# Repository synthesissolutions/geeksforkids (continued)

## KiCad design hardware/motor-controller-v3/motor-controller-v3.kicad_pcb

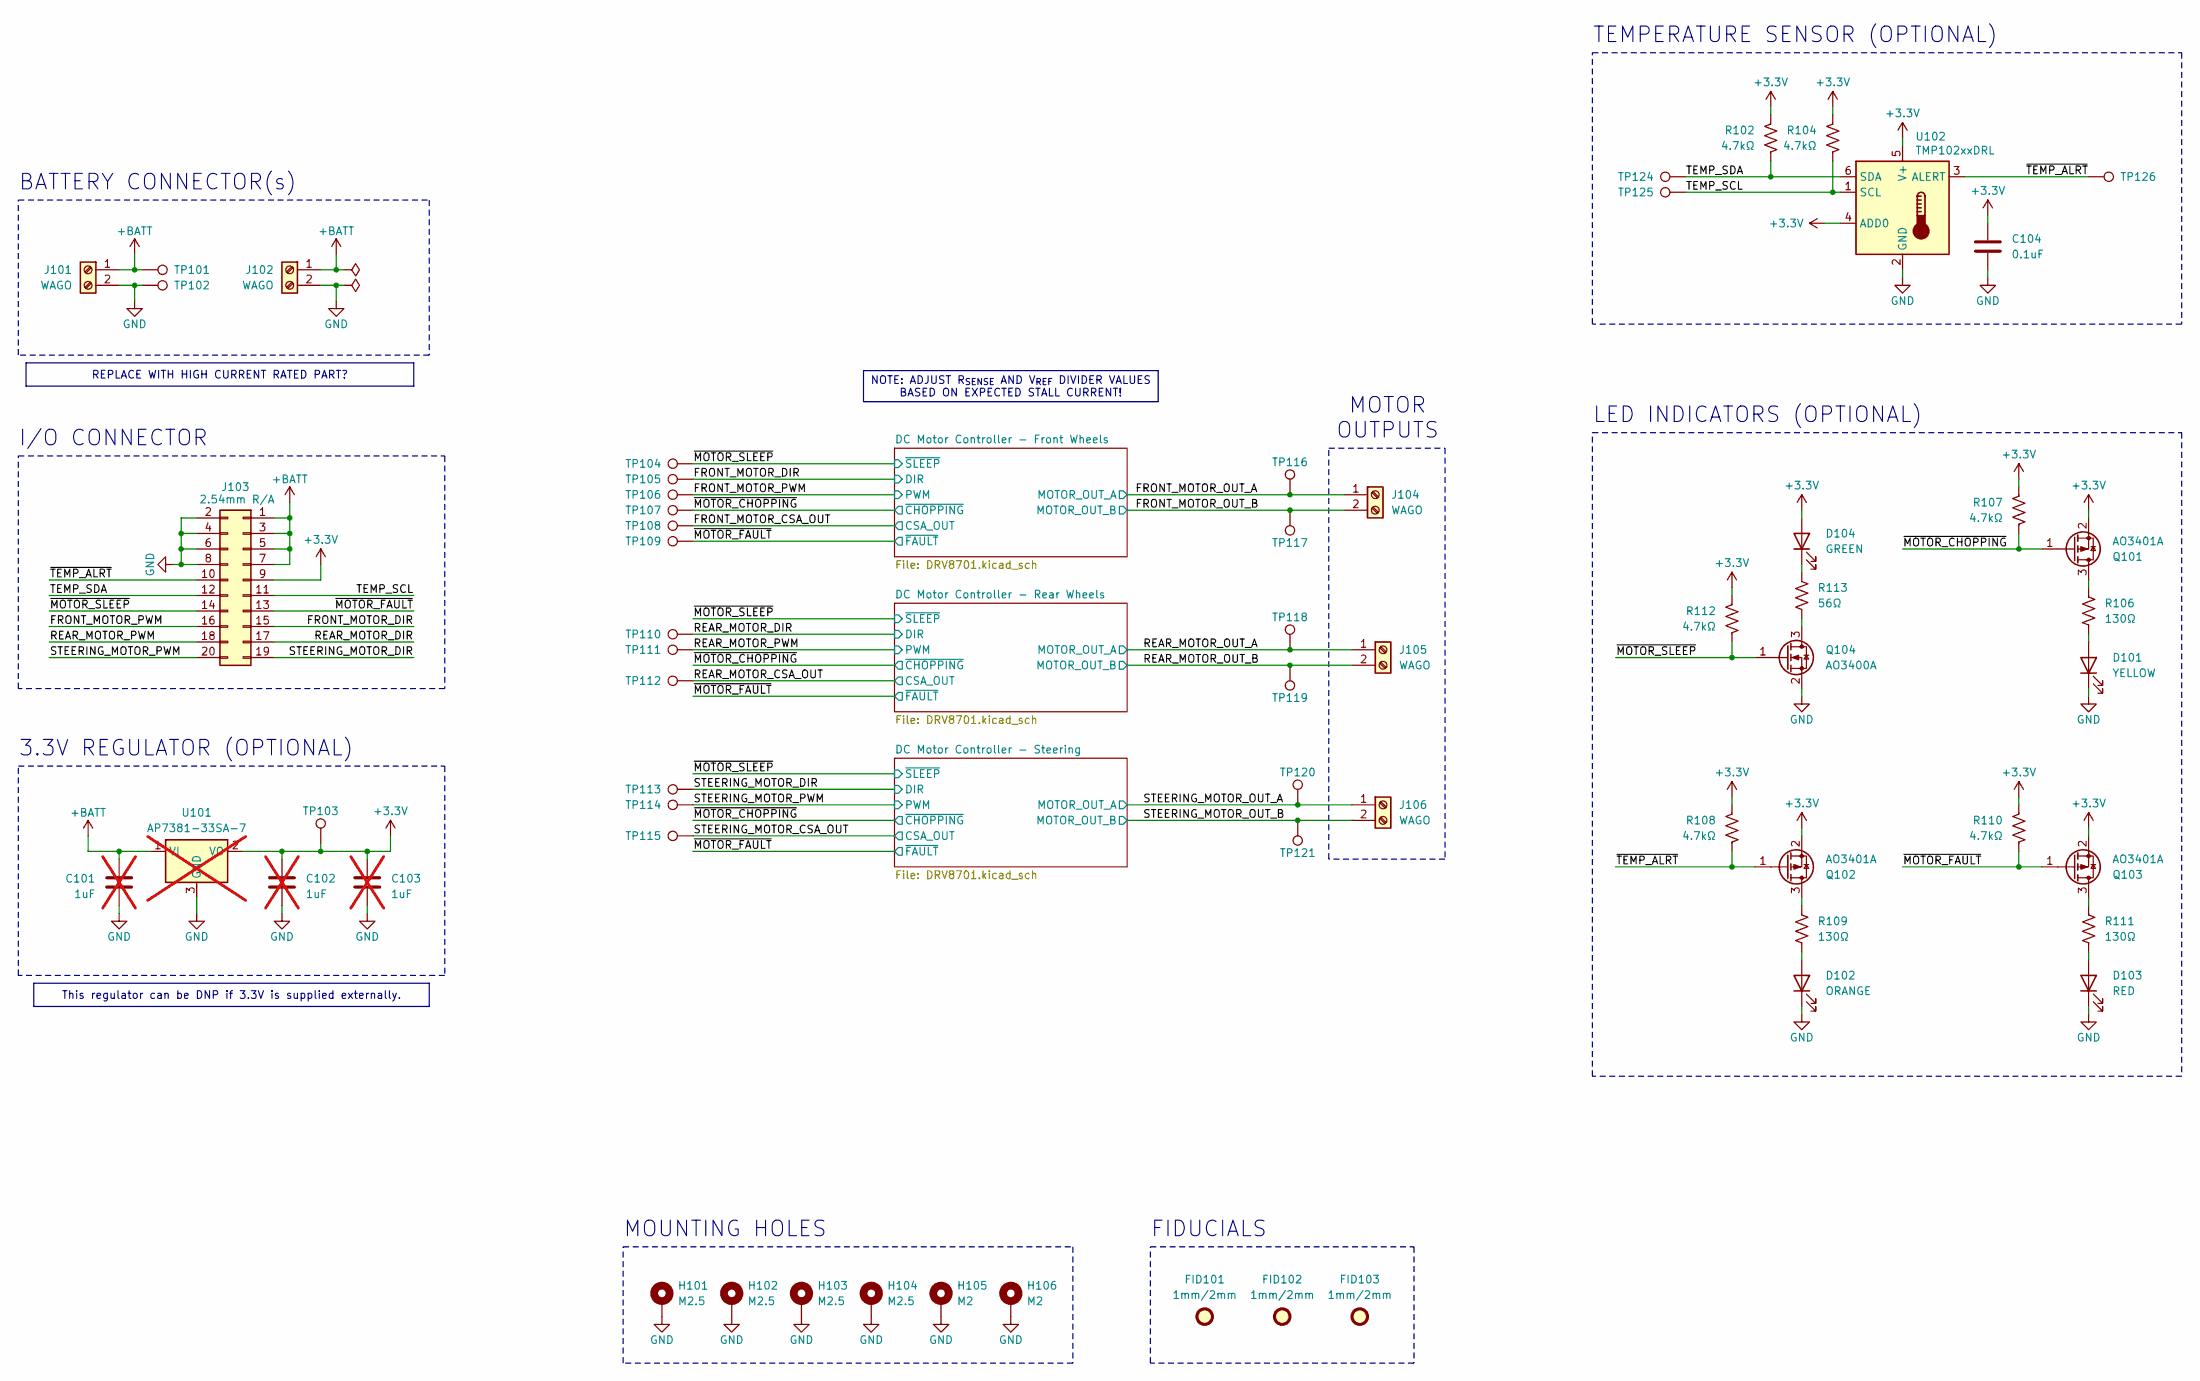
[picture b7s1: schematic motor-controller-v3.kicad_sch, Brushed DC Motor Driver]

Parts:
C101, C102, C103: 1uF; C_0603_1608Metric; MPN C5199872; not fitted
C104: 0.1uF; C_0603_1608Metric; MPN C14663
D101: YELLOW; LED_0603_1608Metric; MPN C965802
D102: ORANGE; LED_0603_1608Metric; MPN C965800
D103: RED; LED_0603_1608Metric; MPN C965799
D104: GREEN; LED_0603_1608Metric; MPN C965804
FID101, FID102, FID103: 1mm/2mm; Fiducial_1mm_Mask2mm
H101, H102, H103, H104: M2.5; MountingHole_2.7mm_M2.5_Pad_Via
H105, H106: M2; MountingHole_2.2mm_M2_Pad_Via
J101, J102, J104, J105, J106: WAGO; TerminalBlock_WAGO_804-302_1x02_P7.50mm_45Degree; MPN 804-302
J103: 2.54mm R/A; PinSocket_2x10_P2.54mm_Horizontal; MPN C2897430
Q101, Q102, Q103: AO3401A; SOT-23; MPN C347476
Q104: AO3400A; SOT-23; MPN C347475
R102, R104, R107, R108, R110, R112: 4.7kΩ; R_0603_1608Metric; MPN C23162
R106, R109, R111: 130Ω; R_0603_1608Metric; MPN C22796
R113: 56Ω; R_0603_1608Metric; MPN C25196
TP101, TP102, TP103, TP104, TP105, TP106, TP107, TP108, TP109, TP110, TP111, TP112, TP113, TP114, TP115, TP116, TP117, TP118, TP119, TP120, TP121, TP124, TP125, TP126: 1.5mm; TestPoint_Pad_D1.5mm
U101: AP7381-33SA-7; SOT-23; MPN C460411; not fitted
U102: TMP102xxDRL; SOT-563; MPN C99269

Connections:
+3.3V: C102.2, C103.2, C104.1, D104.2 (A), J103.9, Q101.2 (S), Q102.2 (S), Q103.2 (S), R102.1, R104.1, R107.1, R108.1, R110.1, R112.1, TP103.1, U101.2 (VO), U102.4 (ADD0), U102.5 (V+)
+BATT: C101.2, J101.1, J102.1, J103.1, J103.3, J103.5, J103.7, TP101.1, U101.1 (VI); also elsewhere on the board
/FRONT_MOTOR_CSA_OUT: TP108.1; also elsewhere on the board
/FRONT_MOTOR_DIR: J103.15, TP105.1; also elsewhere on the board
/FRONT_MOTOR_OUT_A: J104.1, TP116.1; also elsewhere on the board
/FRONT_MOTOR_OUT_B: J104.2, TP117.1; also elsewhere on the board
/FRONT_MOTOR_PWM: J103.16, TP106.1; also elsewhere on the board
/REAR_MOTOR_CSA_OUT: TP112.1; also elsewhere on the board
/REAR_MOTOR_DIR: J103.17, TP110.1; also elsewhere on the board
/REAR_MOTOR_OUT_A: J105.1, TP118.1; also elsewhere on the board
/REAR_MOTOR_OUT_B: J105.2, TP119.1; also elsewhere on the board
/REAR_MOTOR_PWM: J103.18, TP111.1; also elsewhere on the board
/STEERING_MOTOR_CSA_OUT: TP115.1; also elsewhere on the board
/STEERING_MOTOR_DIR: J103.19, TP113.1; also elsewhere on the board
/STEERING_MOTOR_OUT_A: J106.1, TP120.1; also elsewhere on the board
/STEERING_MOTOR_OUT_B: J106.2, TP121.1; also elsewhere on the board
/STEERING_MOTOR_PWM: J103.20, TP114.1; also elsewhere on the board
/TEMP_SCL: J103.11, R104.2, TP125.1, U102.1 (SCL)
/TEMP_SDA: J103.12, R102.2, TP124.1, U102.6 (SDA)
/~MOTOR_CHOPPING: Q101.1 (G), R107.2, TP107.1; also elsewhere on the board
/~MOTOR_FAULT: J103.13, Q103.1 (G), R110.2, TP109.1; also elsewhere on the board
/~MOTOR_SLEEP: J103.14, Q104.1 (G), R112.2, TP104.1; also elsewhere on the board
/~TEMP_ALRT: J103.10, Q102.1 (G), R108.2, TP126.1, U102.3 (ALERT)
GND: C101.1, C102.1, C103.1, C104.2, D101.1 (K), D102.1 (K), D103.1 (K), H101.1, H102.1, H103.1, H104.1, H105.1, H106.1, J101.2, J102.2, J103.2, J103.4, J103.6, J103.8, Q104.2 (S), TP102.1, U101.3 (GND), U102.2 (GND); also elsewhere on the board
unnamed: D101.2 (A), R106.2
unnamed: D102.2 (A), R109.2
unnamed: D103.2 (A), R111.2
unnamed: D104.1 (K), R113.1
unnamed: Q101.3 (D), R106.1
unnamed: Q102.3 (D), R109.1
unnamed: Q103.3 (D), R111.1
unnamed: Q104.3 (D), R113.2

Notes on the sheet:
LED INDICATORS (OPTIONAL)
3.3V REGULATOR (OPTIONAL)
MOUNTING HOLES
MOTOR OUTPUTS
BATTERY CONNECTOR(s)
TEMPERATURE SENSOR (OPTIONAL)
I/O CONNECTOR
FIDUCIALS
This regulator can be DNP if 3.3V is supplied externally.
REPLACE WITH HIGH CURRENT RATED PART?
NOTE: ADJUST R_{SENSE} AND V_{REF} DIVIDER VALUES BASED ON EXPECTED STALL CURRENT!

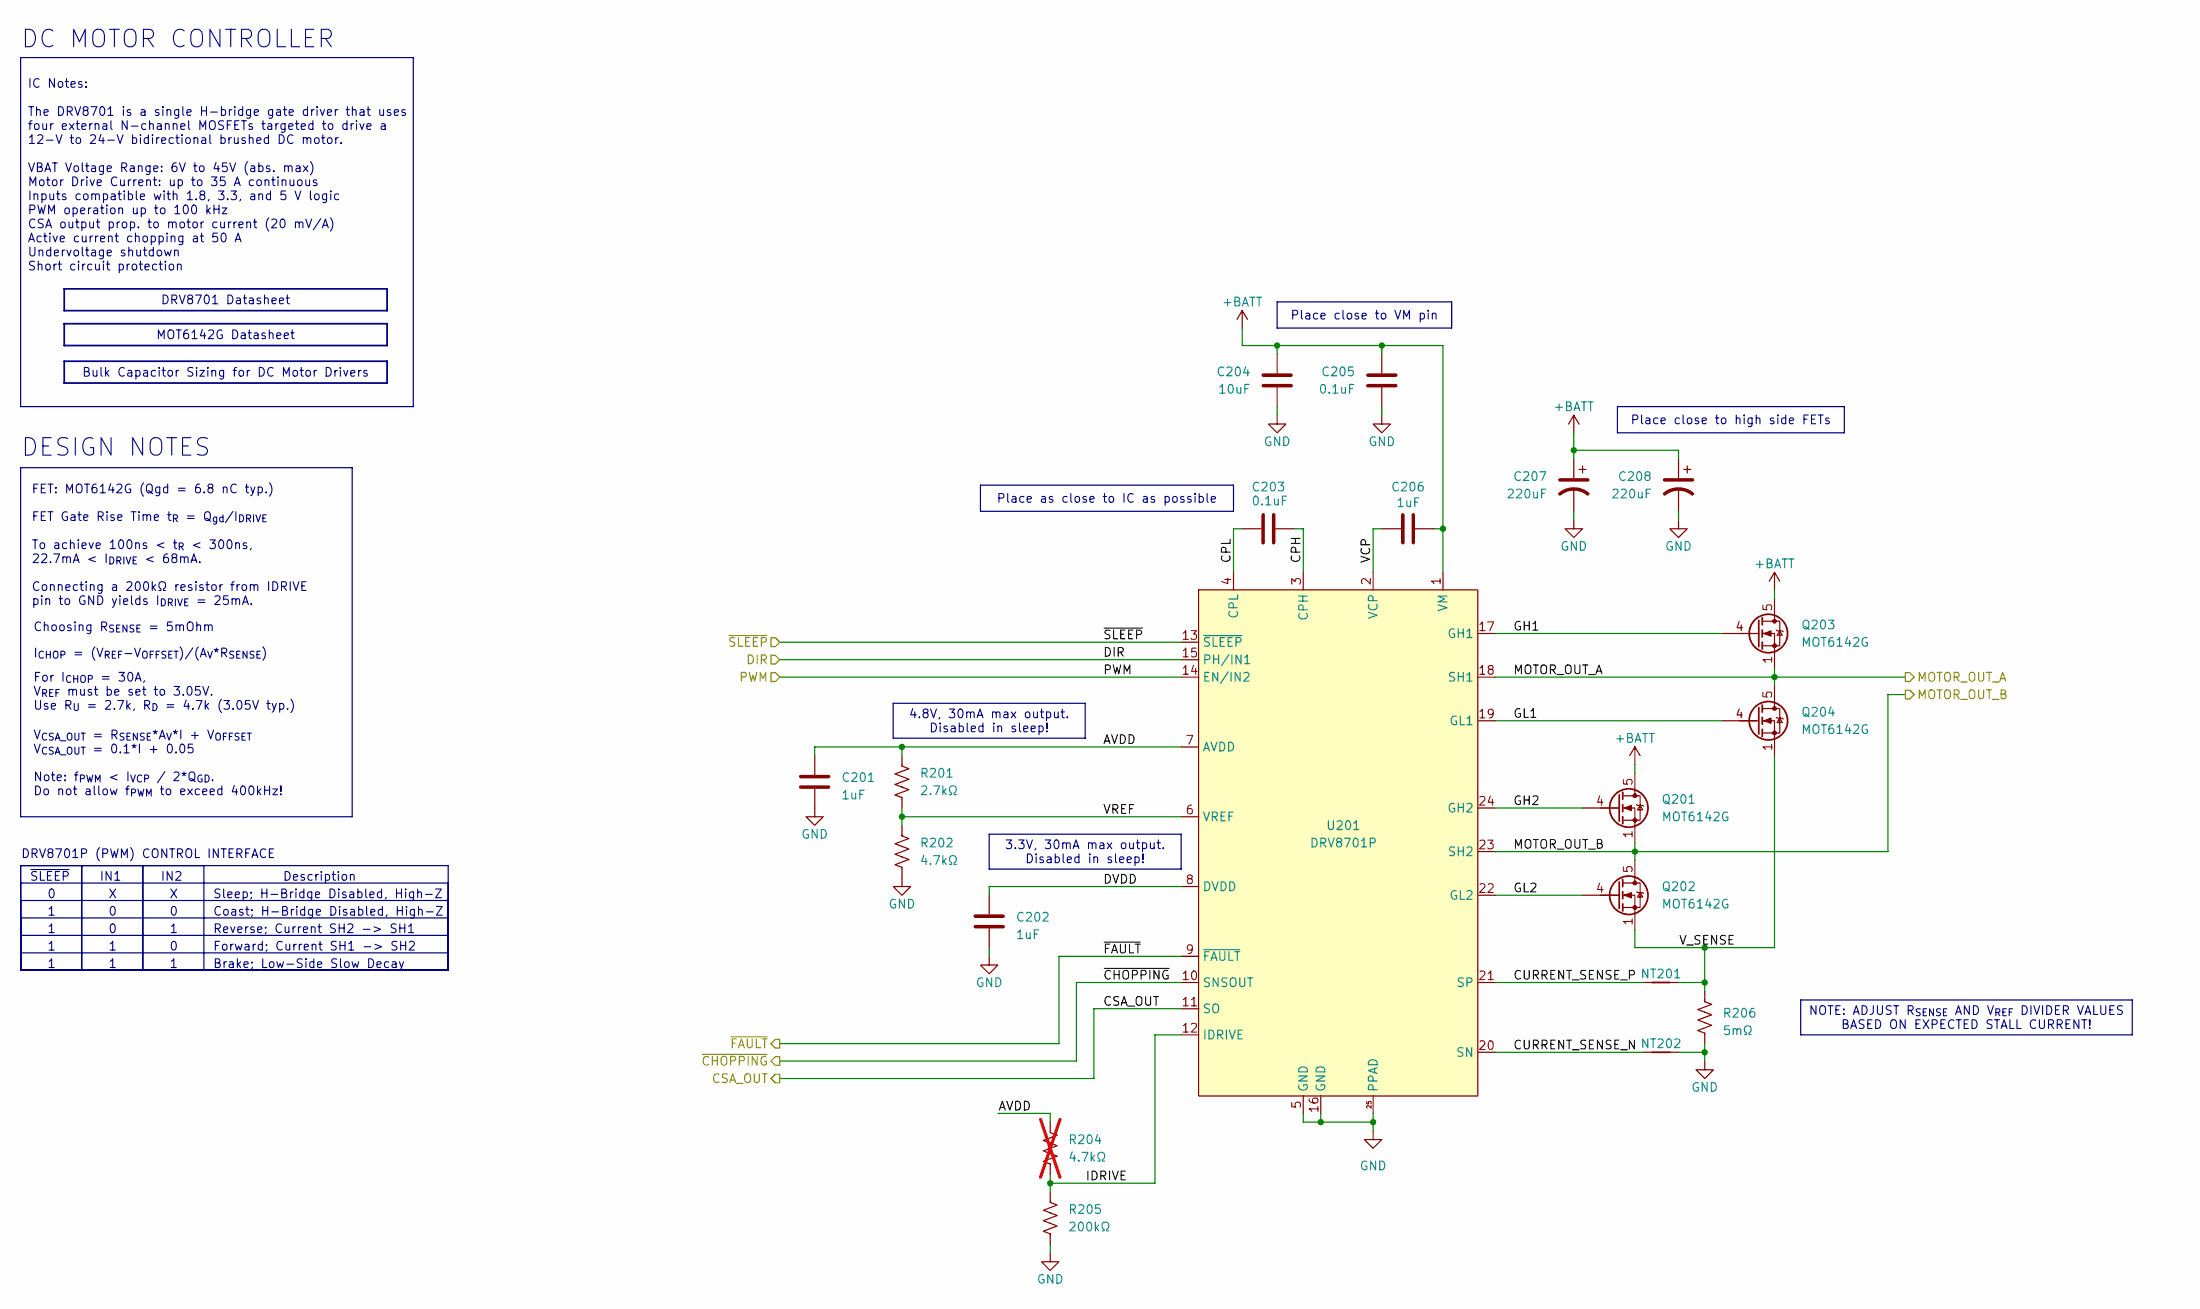
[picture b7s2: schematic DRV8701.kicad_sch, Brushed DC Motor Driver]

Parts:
C201, C202, C206: 1uF; C_0603_1608Metric; MPN C5199872
C203, C205: 0.1uF; C_0603_1608Metric; MPN C14663
C204: 10uF; C_1206_3216Metric; MPN C89632
C207, C208: 220uF; CP_Radial_D10.0mm_P5.00mm; MPN C45105
NT201, NT202: NetTie_2; NetTie-2_SMD_Pad0.5mm
Q201, Q202, Q203, Q204: MOT6142G; PQFN-8-EP_6x5mm_P1.27mm_Generic; MPN C33129541
R201: 2.7kΩ; R_0603_1608Metric; MPN C13167
R202: 4.7kΩ; R_0603_1608Metric; MPN C23162
R204: 4.7kΩ; R_0603_1608Metric; MPN C23162; not fitted
R205: 200kΩ; R_0603_1608Metric; MPN C25811
R206: 5mΩ; DSLR-M_K-3; MPN C41382686
U201: DRV8701P; Texas_RGE0024H_VQFN-24-1EP_4x4mm_P0.5mm_EP2.7x2.7mm; MPN C114178

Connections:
+BATT: C204.2, C205.1, C206.2, C207.1, C208.1, Q201.5 (D), Q203.5 (D), U201.1 (VM); also elsewhere on the board
/DC Motor Controller - Front Wheels/AVDD: C201.2, R201.1, R204.1, U201.7 (AVDD)
/DC Motor Controller - Front Wheels/CPH: C203.1, U201.3 (CPH)
/DC Motor Controller - Front Wheels/CPL: C203.2, U201.4 (CPL)
/DC Motor Controller - Front Wheels/CURRENT_SENSE_N: NT202.1, U201.20 (SN)
/DC Motor Controller - Front Wheels/CURRENT_SENSE_P: NT201.2, U201.21 (SP)
/DC Motor Controller - Front Wheels/DVDD: C202.2, U201.8 (DVDD)
/DC Motor Controller - Front Wheels/GH1: Q203.4 (G), U201.17 (GH1)
/DC Motor Controller - Front Wheels/GH2: Q201.4 (G), U201.24 (GH2)
/DC Motor Controller - Front Wheels/GL1: Q204.4 (G), U201.19 (GL1)
/DC Motor Controller - Front Wheels/GL2: Q202.4 (G), U201.22 (GL2)
/DC Motor Controller - Front Wheels/IDRIVE: R204.2, R205.1, U201.12 (IDRIVE)
/DC Motor Controller - Front Wheels/VCP: C206.1, U201.2 (VCP)
/DC Motor Controller - Front Wheels/VREF: R201.2, R202.1, U201.6 (VREF)
/DC Motor Controller - Front Wheels/V_SENSE: NT201.1, Q202.1 (S), Q202.2 (S), Q202.3 (S), Q204.1 (S), Q204.2 (S), Q204.3 (S), R206.1
/FRONT_MOTOR_CSA_OUT: U201.11 (SO); also elsewhere on the board
/FRONT_MOTOR_DIR: U201.15 (PH/IN1); also elsewhere on the board
/FRONT_MOTOR_OUT_A: Q203.1 (S), Q203.2 (S), Q203.3 (S), Q204.5 (D), U201.18 (SH1); also elsewhere on the board
/FRONT_MOTOR_OUT_B: Q201.1 (S), Q201.2 (S), Q201.3 (S), Q202.5 (D), U201.23 (SH2); also elsewhere on the board
/FRONT_MOTOR_PWM: U201.14 (EN/IN2); also elsewhere on the board
/~MOTOR_CHOPPING: U201.10 (SNSOUT); also elsewhere on the board
/~MOTOR_FAULT: U201.9 (~FAULT); also elsewhere on the board
/~MOTOR_SLEEP: U201.13 (~SLEEP); also elsewhere on the board
GND: C201.1, C202.1, C204.1, C205.2, C207.2, C208.2, NT202.2, R202.2, R205.2, R206.2, U201.5 (GND), U201.16 (GND), U201.25 (PPAD); also elsewhere on the board

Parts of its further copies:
C301, C302, C306, C401, C402, C406: 1uF; C_0603_1608Metric; MPN C5199872
C303, C305, C403, C405: 0.1uF; C_0603_1608Metric; MPN C14663
C304, C404: 10uF; C_1206_3216Metric; MPN C89632
C307, C308, C407, C408: 220uF; CP_Radial_D10.0mm_P5.00mm; MPN C45105
NT301, NT302, NT401, NT402: NetTie_2; NetTie-2_SMD_Pad0.5mm
Q301, Q302, Q303, Q304, Q401, Q402, Q403, Q404: MOT6142G; PQFN-8-EP_6x5mm_P1.27mm_Generic; MPN C33129541
R301, R401: 2.7kΩ; R_0603_1608Metric; MPN C13167
R302, R402: 4.7kΩ; R_0603_1608Metric; MPN C23162
R304, R404: 4.7kΩ; R_0603_1608Metric; MPN C23162; not fitted
R305, R405: 200kΩ; R_0603_1608Metric; MPN C25811
R306, R406: 5mΩ; DSLR-M_K-3; MPN C41382686
U301, U401: DRV8701P; Texas_RGE0024H_VQFN-24-1EP_4x4mm_P0.5mm_EP2.7x2.7mm; MPN C114178

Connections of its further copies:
+BATT: C304.2, C305.1, C306.2, C307.1, C308.1, C404.2, C405.1, C406.2, C407.1, C408.1, Q301.5 (D), Q303.5 (D), Q401.5 (D), Q403.5 (D), U301.1 (VM), U401.1 (VM); also elsewhere on the board
/DC Motor Controller - Rear Wheels/AVDD: C301.2, R301.1, R304.1, U301.7 (AVDD)
/DC Motor Controller - Rear Wheels/CPH: C303.1, U301.3 (CPH)
/DC Motor Controller - Rear Wheels/CPL: C303.2, U301.4 (CPL)
/DC Motor Controller - Rear Wheels/CURRENT_SENSE_N: NT302.1, U301.20 (SN)
/DC Motor Controller - Rear Wheels/CURRENT_SENSE_P: NT301.2, U301.21 (SP)
/DC Motor Controller - Rear Wheels/DVDD: C302.2, U301.8 (DVDD)
/DC Motor Controller - Rear Wheels/GH1: Q303.4 (G), U301.17 (GH1)
/DC Motor Controller - Rear Wheels/GH2: Q301.4 (G), U301.24 (GH2)
/DC Motor Controller - Rear Wheels/GL1: Q304.4 (G), U301.19 (GL1)
/DC Motor Controller - Rear Wheels/GL2: Q302.4 (G), U301.22 (GL2)
/DC Motor Controller - Rear Wheels/IDRIVE: R304.2, R305.1, U301.12 (IDRIVE)
/DC Motor Controller - Rear Wheels/VCP: C306.1, U301.2 (VCP)
/DC Motor Controller - Rear Wheels/VREF: R301.2, R302.1, U301.6 (VREF)
/DC Motor Controller - Rear Wheels/V_SENSE: NT301.1, Q302.1 (S), Q302.2 (S), Q302.3 (S), Q304.1 (S), Q304.2 (S), Q304.3 (S), R306.1
/DC Motor Controller - Steering/AVDD: C401.2, R401.1, R404.1, U401.7 (AVDD)
/DC Motor Controller - Steering/CPH: C403.1, U401.3 (CPH)
/DC Motor Controller - Steering/CPL: C403.2, U401.4 (CPL)
/DC Motor Controller - Steering/CURRENT_SENSE_N: NT402.1, U401.20 (SN)
/DC Motor Controller - Steering/CURRENT_SENSE_P: NT401.2, U401.21 (SP)
/DC Motor Controller - Steering/DVDD: C402.2, U401.8 (DVDD)
/DC Motor Controller - Steering/GH1: Q403.4 (G), U401.17 (GH1)
/DC Motor Controller - Steering/GH2: Q401.4 (G), U401.24 (GH2)
/DC Motor Controller - Steering/GL1: Q404.4 (G), U401.19 (GL1)
/DC Motor Controller - Steering/GL2: Q402.4 (G), U401.22 (GL2)
/DC Motor Controller - Steering/IDRIVE: R404.2, R405.1, U401.12 (IDRIVE)
/DC Motor Controller - Steering/VCP: C406.1, U401.2 (VCP)
/DC Motor Controller - Steering/VREF: R401.2, R402.1, U401.6 (VREF)
/DC Motor Controller - Steering/V_SENSE: NT401.1, Q402.1 (S), Q402.2 (S), Q402.3 (S), Q404.1 (S), Q404.2 (S), Q404.3 (S), R406.1
/REAR_MOTOR_CSA_OUT: U301.11 (SO); also elsewhere on the board
/REAR_MOTOR_DIR: U301.15 (PH/IN1); also elsewhere on the board
/REAR_MOTOR_OUT_A: Q303.1 (S), Q303.2 (S), Q303.3 (S), Q304.5 (D), U301.18 (SH1); also elsewhere on the board
/REAR_MOTOR_OUT_B: Q301.1 (S), Q301.2 (S), Q301.3 (S), Q302.5 (D), U301.23 (SH2); also elsewhere on the board
/REAR_MOTOR_PWM: U301.14 (EN/IN2); also elsewhere on the board
/STEERING_MOTOR_CSA_OUT: U401.11 (SO); also elsewhere on the board
/STEERING_MOTOR_DIR: U401.15 (PH/IN1); also elsewhere on the board
/STEERING_MOTOR_OUT_A: Q403.1 (S), Q403.2 (S), Q403.3 (S), Q404.5 (D), U401.18 (SH1); also elsewhere on the board
/STEERING_MOTOR_OUT_B: Q401.1 (S), Q401.2 (S), Q401.3 (S), Q402.5 (D), U401.23 (SH2); also elsewhere on the board
/STEERING_MOTOR_PWM: U401.14 (EN/IN2); also elsewhere on the board
/~MOTOR_CHOPPING: U301.10 (SNSOUT), U401.10 (SNSOUT); also elsewhere on the board
/~MOTOR_FAULT: U301.9 (~FAULT), U401.9 (~FAULT); also elsewhere on the board
/~MOTOR_SLEEP: U301.13 (~SLEEP), U401.13 (~SLEEP); also elsewhere on the board
GND: C301.1, C302.1, C304.1, C305.2, C307.2, C308.2, C401.1, C402.1, C404.1, C405.2, C407.2, C408.2, NT302.2, NT402.2, R302.2, R305.2, R306.2, R402.2, R405.2, R406.2, U301.5 (GND), U301.16 (GND), U301.25 (PPAD), U401.5 (GND), U401.16 (GND), U401.25 (PPAD); also elsewhere on the board

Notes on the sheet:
Coast; H-Bridge Disabled, High-Z
DC MOTOR CONTROLLER
Choosing R_{SENSE} = 5mOhm
FET: MOT6142G (Qgd = 6.8 nC typ.)
Sleep; H-Bridge Disabled, High-Z
Reverse; Current SH2 -> SH1
Description
FET Gate Rise Time t_{R} = Q_{gd}/I_{DRIVE} To achieve 100ns < t_{R} < 300ns, 22.7mA < I_{DRIVE} < 68mA.
For I_{CHOP} = 30A, V_{REF} must be set to 3.05V. Use R_{U} = 2.7k, R_{D} = 4.7k (3.05V typ.)
IN2
DESIGN NOTES
Forward; Current SH1 -> SH2
IN1
Brake; Low-Side Slow Decay
Note: f_{PWM} < I_{VCP} / 2*Q_{GD}. Do not allow f_{PWM} to exceed 400kHz!
I_{CHOP} = (V_{REF}-V_{OFFSET})/(A_{V}*R_{SENSE})
Connecting a 200kΩ resistor from IDRIVE pin to GND yields I_{DRIVE} = 25mA.
DRV8701P (PWM) CONTROL INTERFACE
V_{CSA_OUT} = R_{SENSE}*A_{V}*I + V_{OFFSET} V_{CSA_OUT} = 0.1*I + 0.05
~{SLEEP}
4.8V, 30mA max output. Disabled in sleep!
IC Notes: The DRV8701 is a single H-bridge gate driver that uses four external N-channel MOSFETs targeted to drive a 12-V to 24-V bidirectional brushed DC motor. VBAT Voltage Range: 6V to 45V (abs. max) Motor Drive Current: up to 35 A continuous Inputs compatible with 1.8, 3.3, and 5 V logic PWM op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
3.3V, 30mA max output. Disabled in sleep!
Place close to VM pin
MOT6142G Datasheet
DRV8701 Datasheet
Bulk Capacitor Sizing for DC Motor Drivers
NOTE: ADJUST R_{SENSE} AND V_{REF} DIVIDER VALUES BASED ON EXPECTED STALL CURRENT!
Place as close to IC as possible
Place close to high side FETs

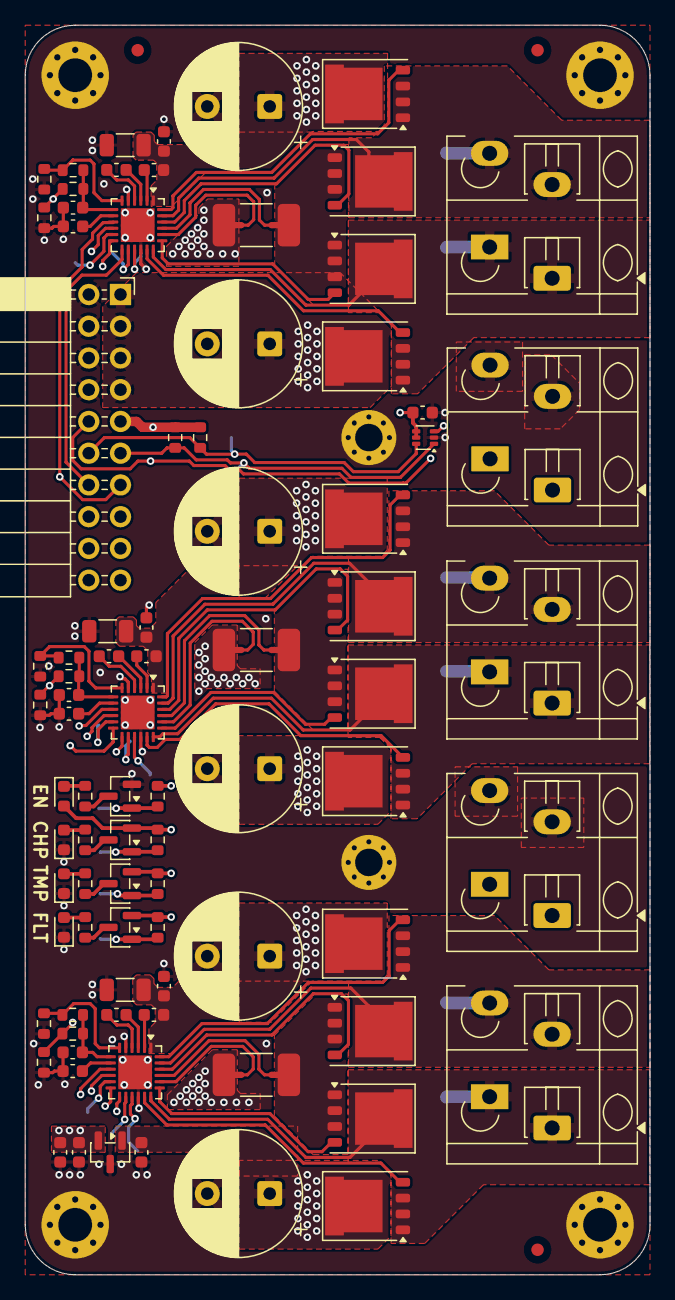
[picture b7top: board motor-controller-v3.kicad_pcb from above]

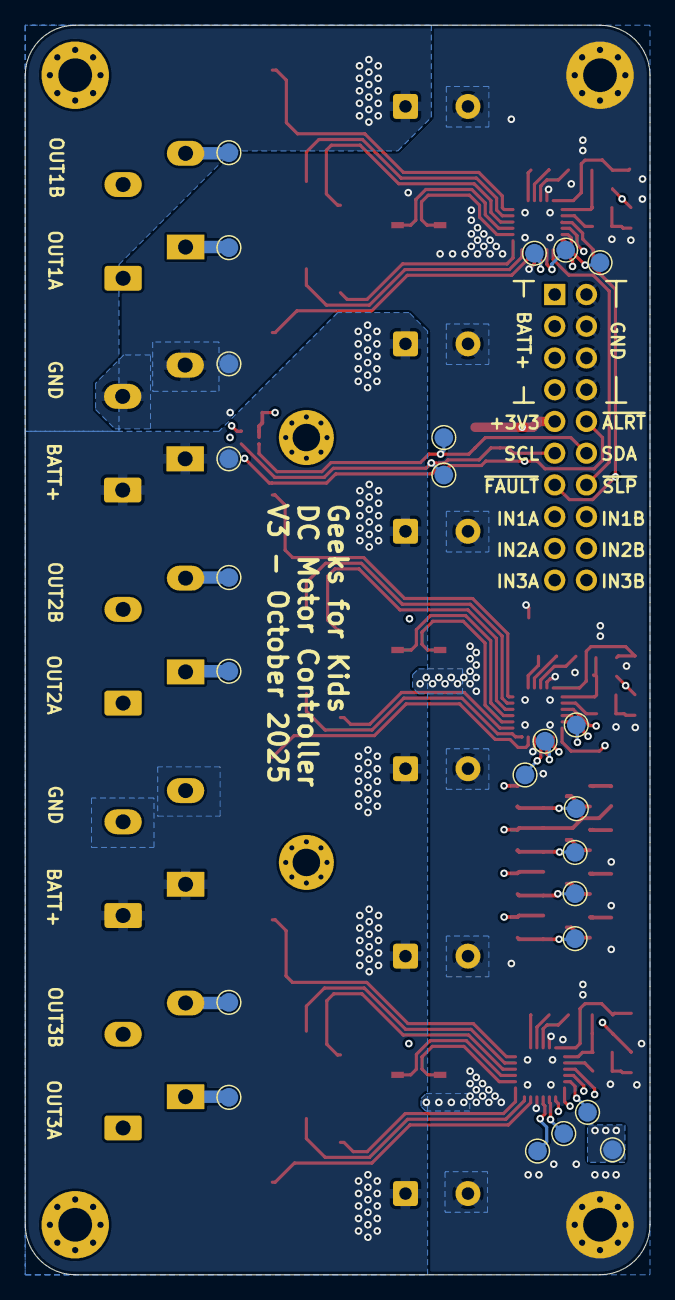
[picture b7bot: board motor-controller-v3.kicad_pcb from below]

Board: 4 copper layers, 50.0 x 100.0 mm, 123 parts (24 on the bottom side), 74 nets.

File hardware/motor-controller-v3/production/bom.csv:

Designator,Footprint,Quantity,Value,LCSC Part #
"C104, C203, C205, C303, C305, C403, C405",0603,7,0.1uF,C14663
"C201, C202, C206, C301, C302, C306, C401, C402, C406",0603,9,1uF,C5199872
"C204, C304, C404",1206,3,10uF,C89632
"C207, C208, C307, C308, C407, C408",CP_Radial_D10.0mm_P5.00mm,6,220uF,C45105
D101,0603,1,YELLOW,C965802
D102,0603,1,ORANGE,C965800
D103,0603,1,RED,C965799
D104,0603,1,GREEN,C965804
"J101, J102, J104, J105, J106",TerminalBlock_WAGO_804-302_1x02_P7.50mm_45Degree,5,WAGO,804-302
J103,PinSocket_2x10_P2.54mm_Horizontal,1,2.54mm R/A,C2897430
"Q101, Q102, Q103",SOT-23,3,AO3401A,C347476
Q104,SOT-23,1,AO3400A,C347475
"Q201, Q202, Q203, Q204, Q301, Q302, Q303, Q304, Q401, Q402, Q403, Q404",PQFN-8-EP_6x5mm_P1.27mm_Generic,12,MOT6142G,C33129541
"R102, R104, R107, R108, R110, R112, R202, R302, R402",0603,9,4.7kΩ,C23162
"R106, R109, R111",0603,3,130Ω,C22796
R113,0603,1,56Ω,C25196
"R201, R301, R401",0603,3,2.7kΩ,C13167
"R205, R305, R405",0603,3,200kΩ,C25811
"R206, R306, R406",DSLR-M_K-3,3,5mΩ,C41382686
U102,SOT-563,1,TMP102xxDRL,C99269
"U201, U301, U401",Texas_RGE0024H_VQFN-24-1EP_4x4mm_P0.5mm_EP2.7x2.7mm,3,DRV8701P,C114178
